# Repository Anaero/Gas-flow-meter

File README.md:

# Gas-flow-meter

The materials in this Repository have been designed to support data logging from the Anaero gas flow meter using a low cost Arduino based system (see http://www.anaero.co.uk/ for more information). All materials available from this repository are available subject to the terms and conditions of the Creative Commons CC BY-SA license (https://creativecommons.org/licenses/by-sa/4.0/).  Please see the licensing document in the repository for more information or visit the Creative Commons Web site.

No warranty, implied or otherwise, is granted in respect of the hardware designs or software available from this repository.

System overview - the hardware

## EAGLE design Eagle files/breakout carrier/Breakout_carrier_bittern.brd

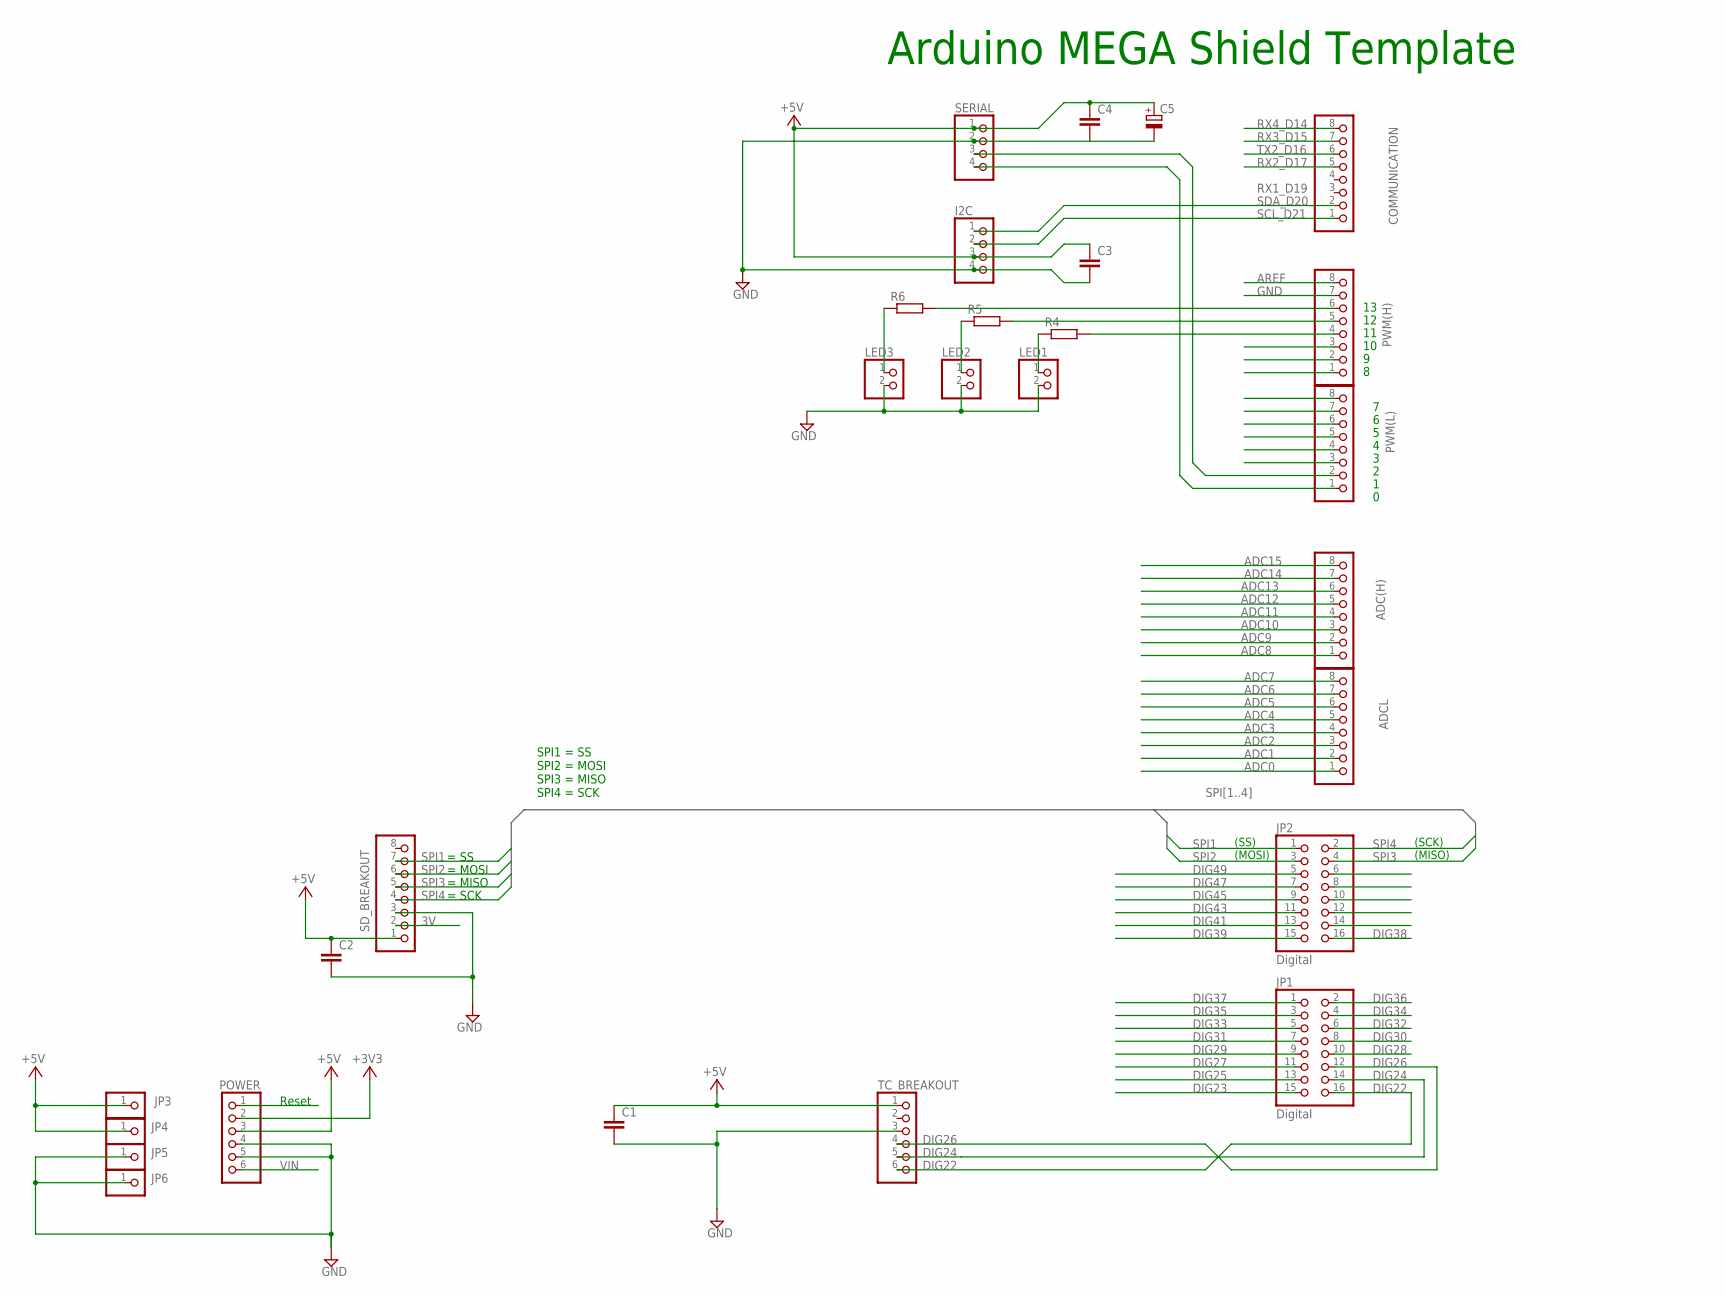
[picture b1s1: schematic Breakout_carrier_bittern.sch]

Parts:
ADC(H): PINHD-1X8; 1X08
ADCL: PINHD-1X8; 1X08
C1, C2, C3, C4: C-EU050-045X075; C050-045X075
C5: CPOL-EUE2.5-6; E2,5-6
COMMUNICATION: PINHD-1X8; 1X08
I2C: PINHD-1X4; 1X04
JP1, JP2: Digital; 2X08
JP3, JP4, JP5, JP6: PINHD-1X1; 1X01
LED1, LED2, LED3: PINHD-1X2; 1X02
POWER: PINHD-1X6; 1X06
PWM(H): PINHD-1X8; 1X08
PWM(L): PINHD-1X8; 1X08
R4, R5, R6: R-EU_0309/12; 0309/12
SD_BREAKOUT: PINHD-1X8; 1X08
SERIAL: PINHD-1X4; 1X04
TC_BREAKOUT: PINHD-1X6; 1X06

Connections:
3V: SD_BREAKOUT.2
+3V3: POWER.2
+5V: C1.1, C2.1, C3.1, C4.1, C5.+, I2C.3, JP3.1, JP4.1, POWER.3, SD_BREAKOUT.1, SERIAL.1, TC_BREAKOUT.1
ADC0: ADCL.1
ADC1: ADCL.2
ADC2: ADCL.3
ADC3: ADCL.4
ADC4: ADCL.5
ADC5: ADCL.6
ADC6: ADCL.7
ADC7: ADCL.8
ADC8: ADC(H).1
ADC9: ADC(H).2
ADC10: ADC(H).3
ADC11: ADC(H).4
ADC12: ADC(H).5
ADC13: ADC(H).6
ADC14: ADC(H).7
ADC15: ADC(H).8
AREF: PWM(H).8
DIG22: JP1.16, TC_BREAKOUT.6
DIG23: JP1.15
DIG24: JP1.14, TC_BREAKOUT.5
DIG25: JP1.13
DIG26: JP1.12, TC_BREAKOUT.4
DIG27: JP1.11
DIG28: JP1.10
DIG29: JP1.9
DIG30: JP1.8
DIG31: JP1.7
DIG32: JP1.6
DIG33: JP1.5
DIG34: JP1.4
DIG35: JP1.3
DIG36: JP1.2
DIG37: JP1.1
DIG38: JP2.16
DIG39: JP2.15
DIG41: JP2.13
DIG43: JP2.11
DIG45: JP2.9
DIG47: JP2.7
DIG49: JP2.5
GND: C1.2, C2.2, C3.2, C4.2, C5.-, I2C.4, JP5.1, JP6.1, LED1.2, LED2.2, LED3.2, POWER.4, POWER.5, PWM(H).7, SD_BREAKOUT.3, SERIAL.2, TC_BREAKOUT.3
unnamed: PWM(L).2, SERIAL.3
unnamed: PWM(H).4, R4.2
unnamed: PWM(H).5, R5.2
unnamed: PWM(H).6, R6.2
unnamed: LED3.1, R6.1
unnamed: LED2.1, R5.1
unnamed: LED1.1, R4.1
RESET: POWER.1
RX1_D19: PWM(L).1, SERIAL.4
RX2_D17: COMMUNICATION.5
RX3_D15: COMMUNICATION.7
RX4_D14: COMMUNICATION.8
SCL_D21: COMMUNICATION.1, I2C.2
SDA_D20: COMMUNICATION.2, I2C.1
SPI1: JP2.1, SD_BREAKOUT.7
SPI2: JP2.3, SD_BREAKOUT.6
SPI3: JP2.4, SD_BREAKOUT.5
SPI4: JP2.2, SD_BREAKOUT.4
TX2_D16: COMMUNICATION.6
VIN: POWER.6

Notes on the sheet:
Arduino MEGA Shield Template
(SS)
(MOSI)
(SCK)
(MISO)
Reset
= SCK
= MISO
= MOSI
= SS
SPI1 = SS SPI2 = MOSI SPI3 = MISO SPI4 = SCK

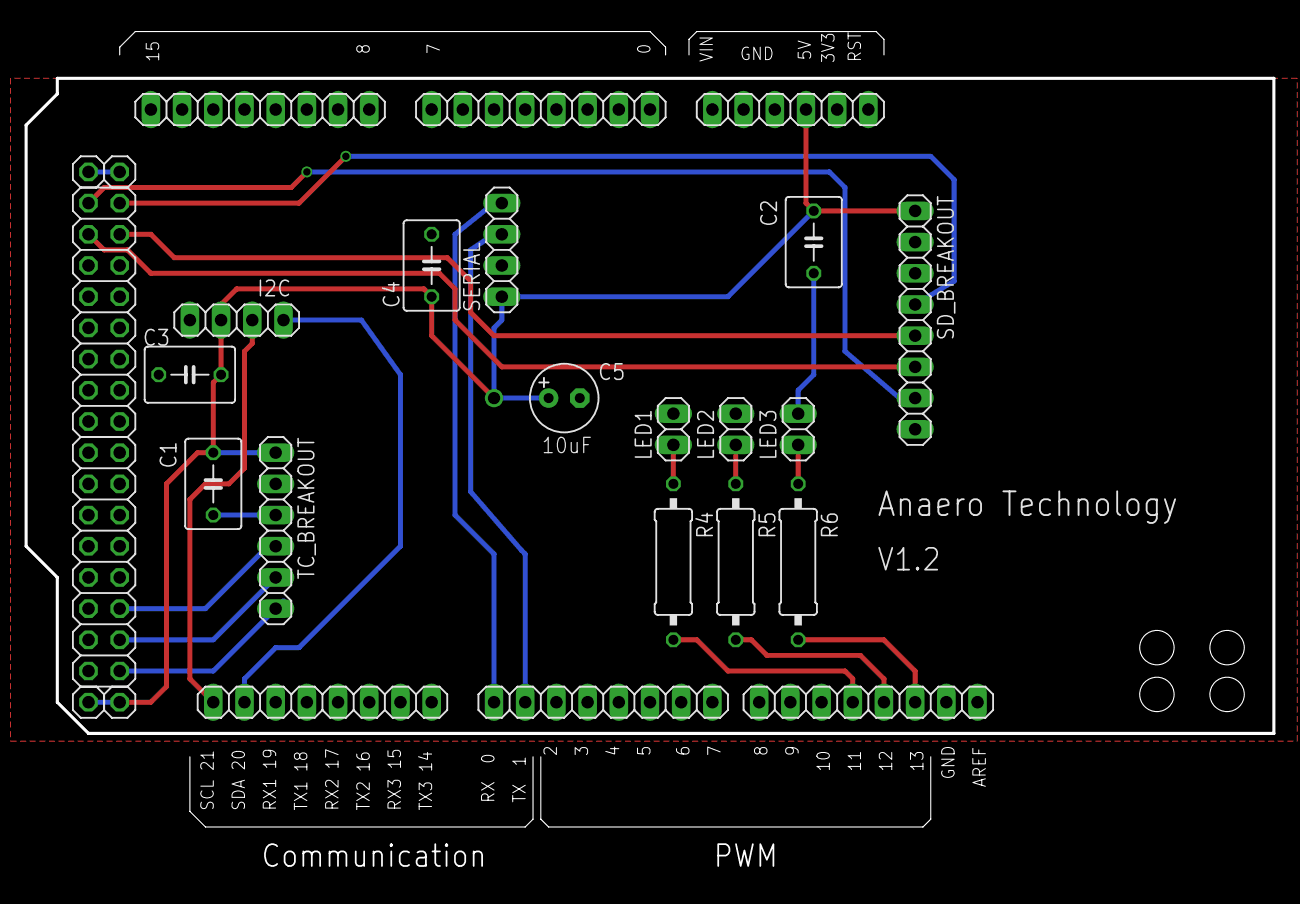
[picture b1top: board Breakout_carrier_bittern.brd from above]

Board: 4 copper layers, 101.6 x 69.3 mm, 27 parts (0 on the bottom side), 19 nets.

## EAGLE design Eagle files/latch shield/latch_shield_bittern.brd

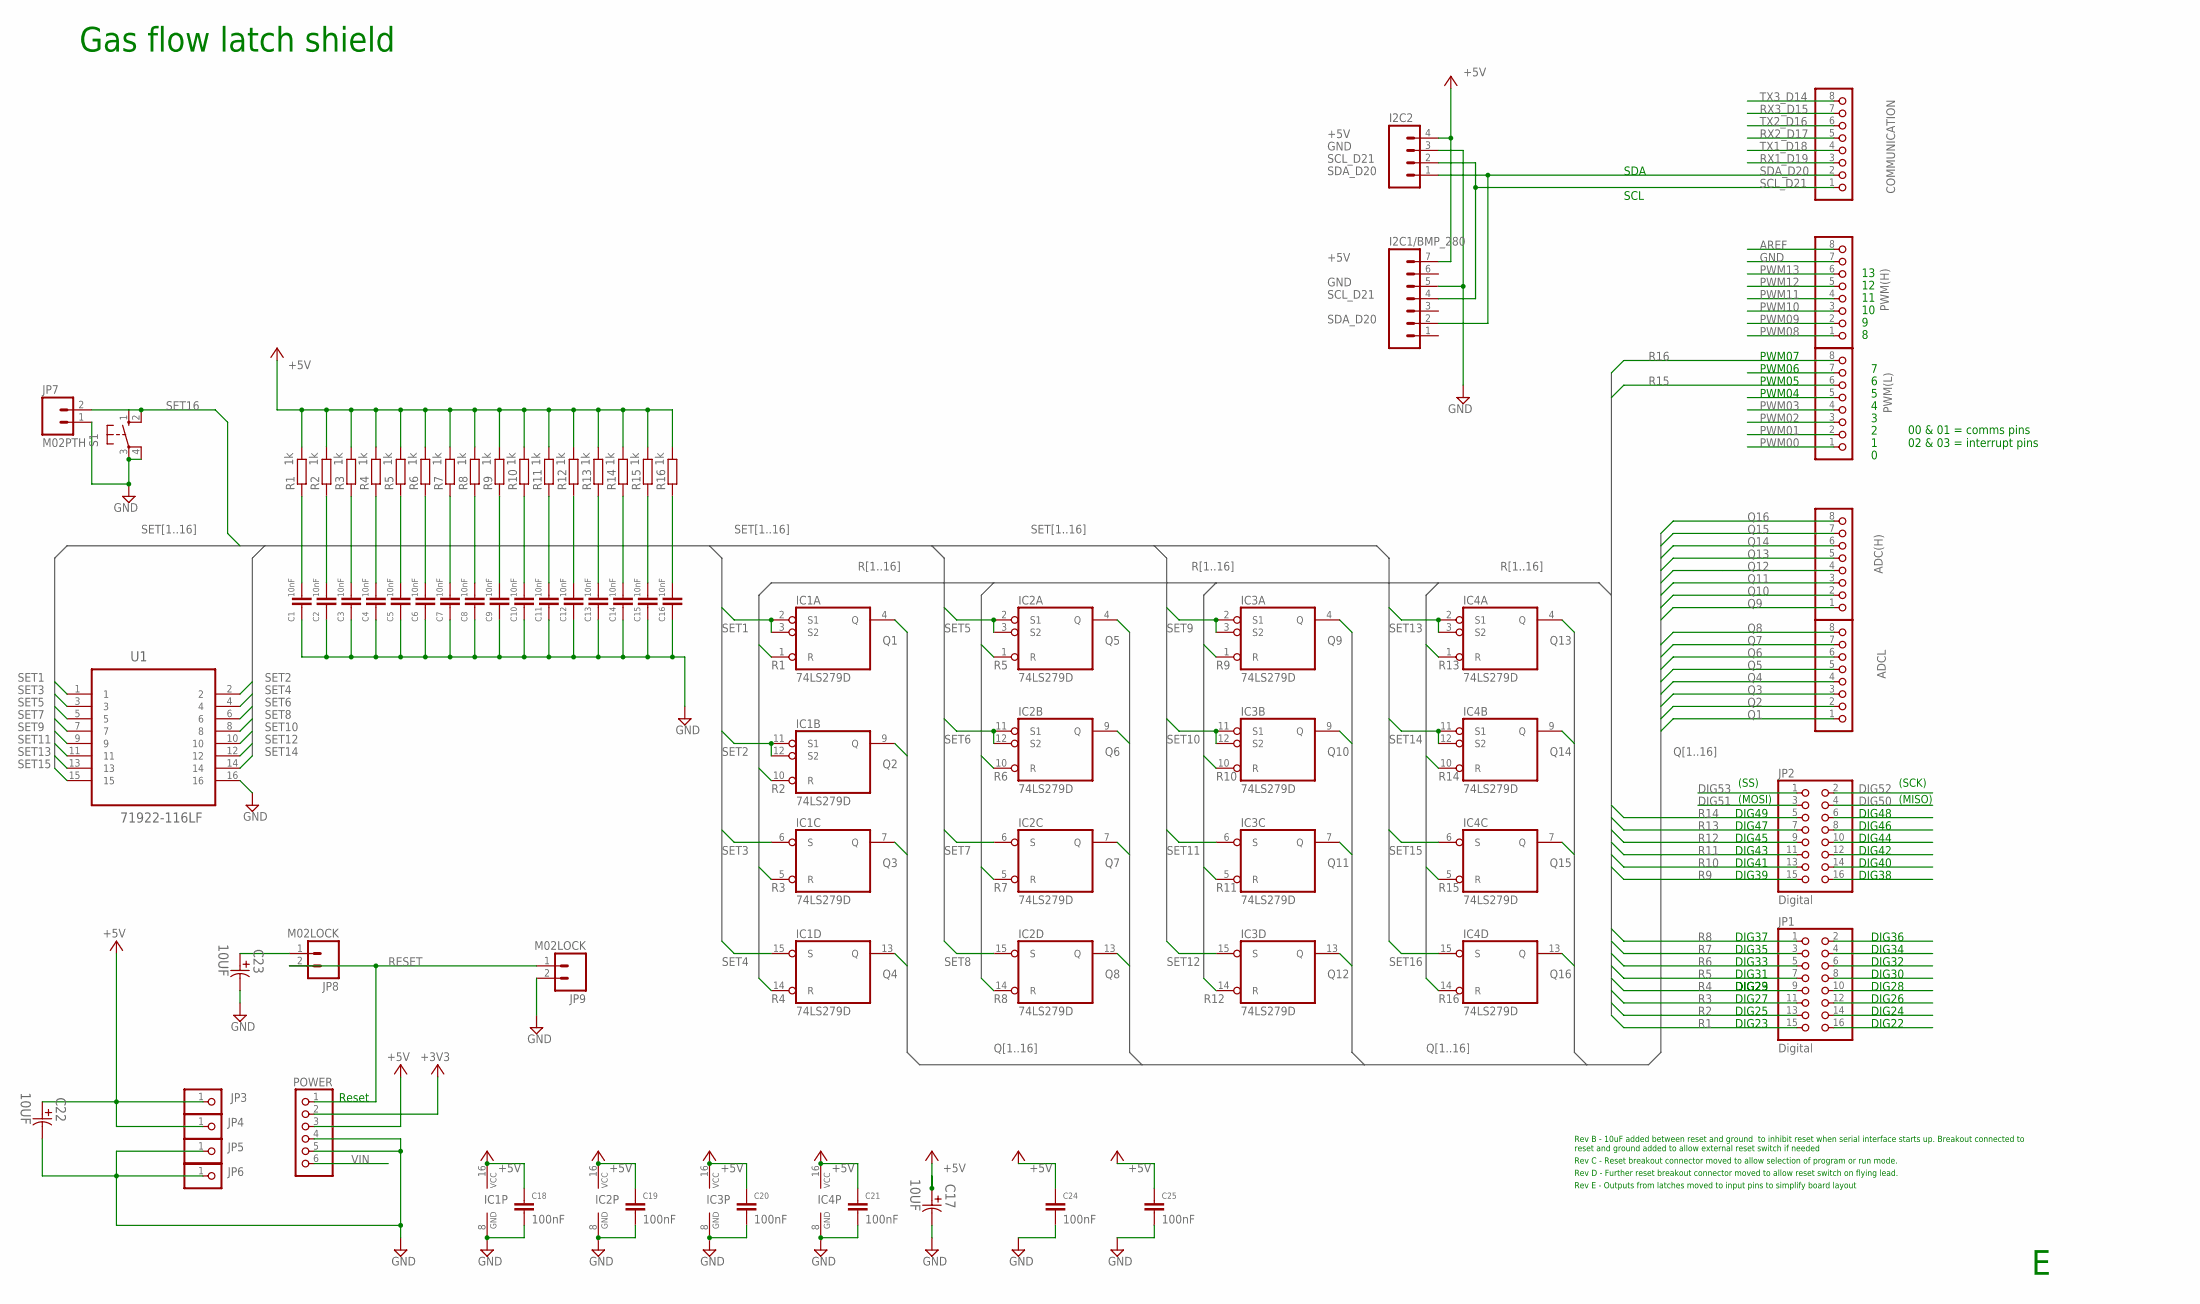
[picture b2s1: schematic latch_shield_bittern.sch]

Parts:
ADC(H): PINHD-1X8; 1X08
ADCL: PINHD-1X8; 1X08
C1, C2, C3, C4, C5, C6, C7, C8, C9, C10, C11, C12, C13, C14, C15, C16: 10nF; C0603
C17, C22, C23: 10UF; CAPAE530X610N
C18, C19, C20, C21, C24, C25: 100nF; C0603
COMMUNICATION: PINHD-1X8; 1X08
I2C1/BMP_280: M07; 1X07
I2C2: M04PTH; 1X04
IC1, IC2, IC3, IC4: 74LS279D; SO16
JP1, JP2: Digital; 2X08
JP3, JP4, JP5, JP6: PINHD-1X1; 1X01
JP7: M02PTH; 1X02
JP8, JP9: M02LOCK; 1X02_LOCK
POWER: PINHD-1X6; 1X06
PWM(H): PINHD-1X8; 1X08
PWM(L): PINHD-1X8; 1X08
R1, R2, R3, R4, R5, R6, R7, R8, R9, R10, R11, R12, R13, R14, R15, R16: 1k; R0603
S1: 10-XX; B3F-10XX
U1: 71922-116LF; FCI_71922-116LF

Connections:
+3V3: POWER.2
+5V: C17.1, C18.1, C19.1, C20.1, C21.1, C22.1, C24.1, C25.1, I2C1/BMP_280.7, I2C2.4, IC1.16 (VCC), IC2.16 (VCC), IC3.16 (VCC), IC4.16 (VCC), JP3.1, JP4.1, POWER.3, R1.2, R2.2, R3.2, R4.2, R5.2, R6.2, R7.2, R8.2, R9.2, R10.2, R11.2, R12.2, R13.2, R14.2, R15.2, R16.2
AREF: PWM(H).8
DIG50: JP2.4
DIG51: JP2.3
DIG52: JP2.2
DIG53: JP2.1
GND: C1.1, C2.1, C3.1, C4.1, C5.1, C6.1, C7.1, C8.1, C9.1, C10.1, C11.1, C12.1, C13.1, C14.1, C15.1, C16.1, C17.2, C18.2, C19.2, C20.2, C21.2, C22.2, C23.2, C24.2, C25.2, I2C1/BMP_280.5, I2C2.3, IC1.8 (GND), IC2.8 (GND), IC3.8 (GND), IC4.8 (GND), JP5.1, JP6.1, JP7.1, JP9.2, POWER.4, POWER.5, PWM(H).7, S1.3, S1.4 (P1), U1.16
unnamed: C23.1, JP8.1
PWM00: PWM(L).1
PWM01: PWM(L).2
PWM02: PWM(L).3
PWM03: PWM(L).4
PWM08: PWM(H).1
PWM09: PWM(H).2
PWM10: PWM(H).3
PWM11: PWM(H).4
PWM12: PWM(H).5
PWM13: PWM(H).6
Q1: ADCL.1, IC1.4 (Q)
Q2: ADCL.2, IC1.9 (Q)
Q3: ADCL.3, IC1.7 (Q)
Q4: ADCL.4, IC1.13 (Q)
Q5: ADCL.5, IC2.4 (Q)
Q6: ADCL.6, IC2.9 (Q)
Q7: ADCL.7, IC2.7 (Q)
Q8: ADCL.8, IC2.13 (Q)
Q9: ADC(H).1, IC3.4 (Q)
Q10: ADC(H).2, IC3.9 (Q)
Q11: ADC(H).3, IC3.7 (Q)
Q12: ADC(H).4, IC3.13 (Q)
Q13: ADC(H).5, IC4.4 (Q)
Q14: ADC(H).6, IC4.9 (Q)
Q15: ADC(H).7, IC4.7 (Q)
Q16: ADC(H).8, IC4.13 (Q)
R1: IC1.1 (R), JP1.15
R2: IC1.10 (R), JP1.13
R3: IC1.5 (R), JP1.11
R4: IC1.14 (R), JP1.9
R5: IC2.1 (R), JP1.7
R6: IC2.10 (R), JP1.5
R7: IC2.5 (R), JP1.3
R8: IC2.14 (R), JP1.1
R9: IC3.1 (R), JP2.15
R10: IC3.10 (R), JP2.13
R11: IC3.5 (R), JP2.11
R12: IC3.14 (R), JP2.9
R13: IC4.1 (R), JP2.7
R14: IC4.10 (R), JP2.5
R15: IC4.5 (R), PWM(L).6
R16: IC4.14 (R), PWM(L).8
RESET: JP8.2, JP9.1, POWER.1
RX1_D19: COMMUNICATION.3
RX2_D17: COMMUNICATION.5
RX3_D15: COMMUNICATION.7
SCL_D21: COMMUNICATION.1, I2C1/BMP_280.4, I2C2.2
SDA_D20: COMMUNICATION.2, I2C1/BMP_280.2, I2C2.1
SET1: C1.2, IC1.2 (S1), IC1.3 (S2), R1.1, U1.1
SET2: C2.2, IC1.11 (S1), IC1.12 (S2), R2.1, U1.2
SET3: C3.2, IC1.6 (S), R3.1, U1.3
SET4: C4.2, IC1.15 (S), R4.1, U1.4
SET5: C5.2, IC2.2 (S1), IC2.3 (S2), R5.1, U1.5
SET6: C6.2, IC2.11 (S1), IC2.12 (S2), R6.1, U1.6
SET7: C7.2, IC2.6 (S), R7.1, U1.7
SET8: C8.2, IC2.15 (S), R8.1, U1.8
SET9: C9.2, IC3.2 (S1), IC3.3 (S2), R9.1, U1.9
SET10: C10.2, IC3.11 (S1), IC3.12 (S2), R10.1, U1.10
SET11: C11.2, IC3.6 (S), R11.1, U1.11
SET12: C12.2, IC3.15 (S), R12.1, U1.12
SET13: C13.2, IC4.2 (S1), IC4.3 (S2), R13.1, U1.13
SET14: C14.2, IC4.11 (S1), IC4.12 (S2), R14.1, U1.14
SET15: C15.2, IC4.6 (S), R15.1, U1.15
SET16: C16.2, IC4.15 (S), JP7.2, R16.1, S1.1 (S), S1.2 (S1)
TX1_D18: COMMUNICATION.4
TX2_D16: COMMUNICATION.6
TX3_D14: COMMUNICATION.8
VIN: POWER.6

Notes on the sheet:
(SS)
(MOSI)
(SCK)
(MISO)
Reset
DIG22
DIG24
DIG26
DIG28
DIG30
DIG32
DIG34
DIG36
DIG38
DIG40
DIG42
DIG44
DIG46
DIG48
DIG23
DIG25
DIG27
DIG29
DIG31
DIG33
DIG35
DIG37
DIG39
DIG43
DIG41
DIG45
DIG47
DIG49
PWM07
PWM05
PWM04
PWM06
00 & 01 = comms pins 02 & 03 = interrupt pins
SDA
SCL

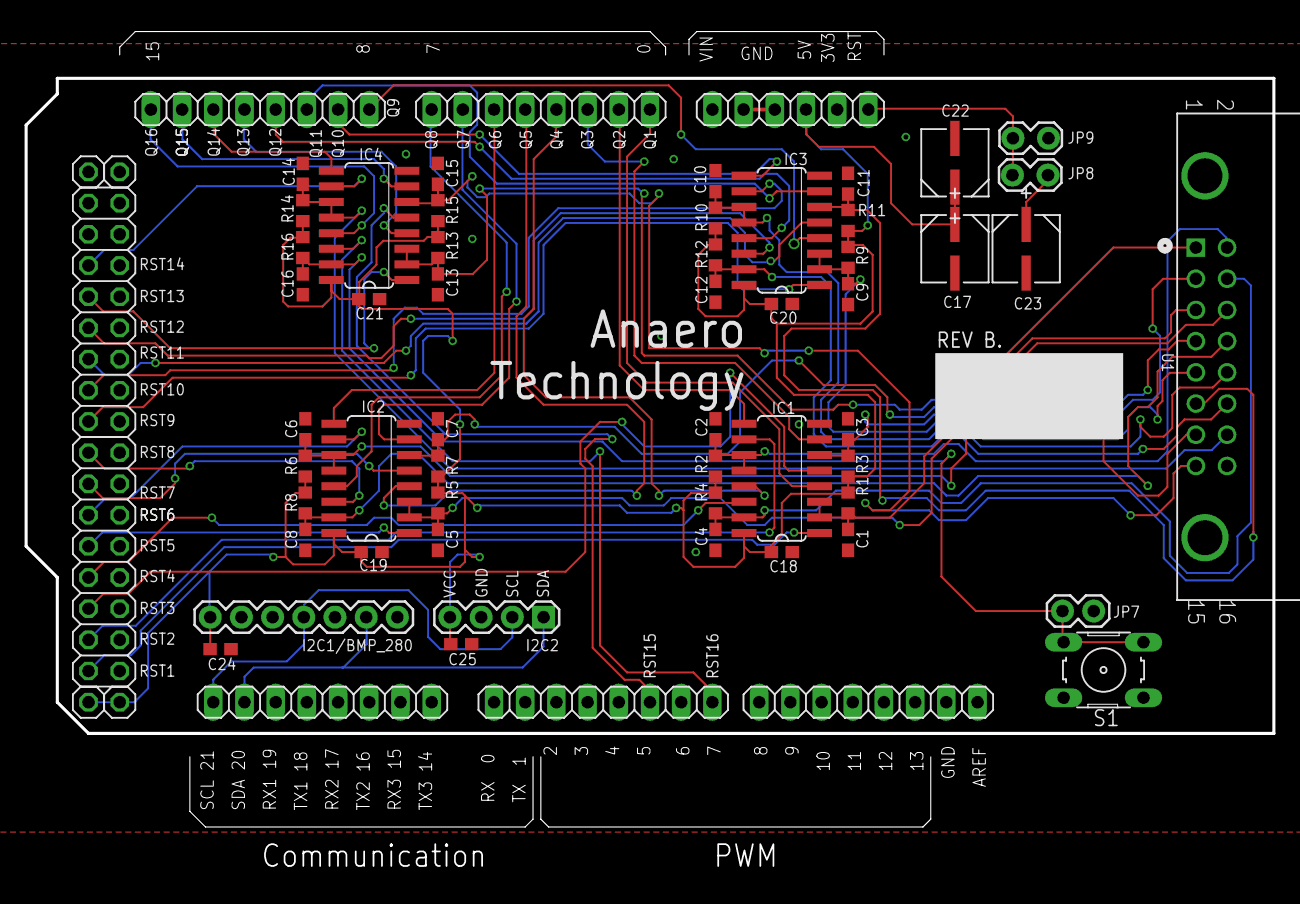
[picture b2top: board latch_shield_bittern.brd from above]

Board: 4 copper layers, 101.6 x 69.3 mm, 64 parts (0 on the bottom side), 54 nets.

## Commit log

2017-06-01 Create Licensing
2017-06-01 Update Licensing
2017-06-06 Add files via upload
    Arduino source code for Bittern build
2017-06-06 Overview of Python utilities
2017-06-06 Arduino code for data logger
2017-06-06 Bittern build
2017-06-06 Read2 title
2017-06-06 License terms & conditions
2017-06-06 Python utilities
2017-06-06 startrun source
2017-06-06 monitor source
2017-06-06 filegrab source
2017-06-06 fastgrab source
2017-06-06 Overview
2017-06-06 Licensing terms and conditions (CC BY-SA)
2017-06-06 schematic
2017-06-06 board layout
2017-06-06 .exe file for 32 bit Windows 10 machines
2017-06-06 setup template
2017-06-06 .exe file for 64 bit Windows 10 machines
2017-06-06 Eagle files for application specific pcbs
2017-06-06 .exe versions of Python utilities (64 bit Windows 10 machines)
2017-06-06 .exe 32 bit Windows 10
2017-06-06 .exe versions of Python utilities (32 bit Windows 10 machines)
2017-06-12 Breakout carrier
2017-06-12 latch shield .sch and .brd files
2017-06-12 breakout carrier .sch and .brd files
2017-06-12 application specific pcb design files
2017-06-14 fastgrab source V2
2017-06-14 filegrab source V2
2017-06-14 version 2 .exe file for 64 bit Windows 10 machines
2020-11-17 Python executables
2020-11-17 New executables

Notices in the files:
parts and their libraries:
SparkFun-Connectors: Licensing: CC v3.0 Share-Alike You are welcome to use this library for commercial purposes.
